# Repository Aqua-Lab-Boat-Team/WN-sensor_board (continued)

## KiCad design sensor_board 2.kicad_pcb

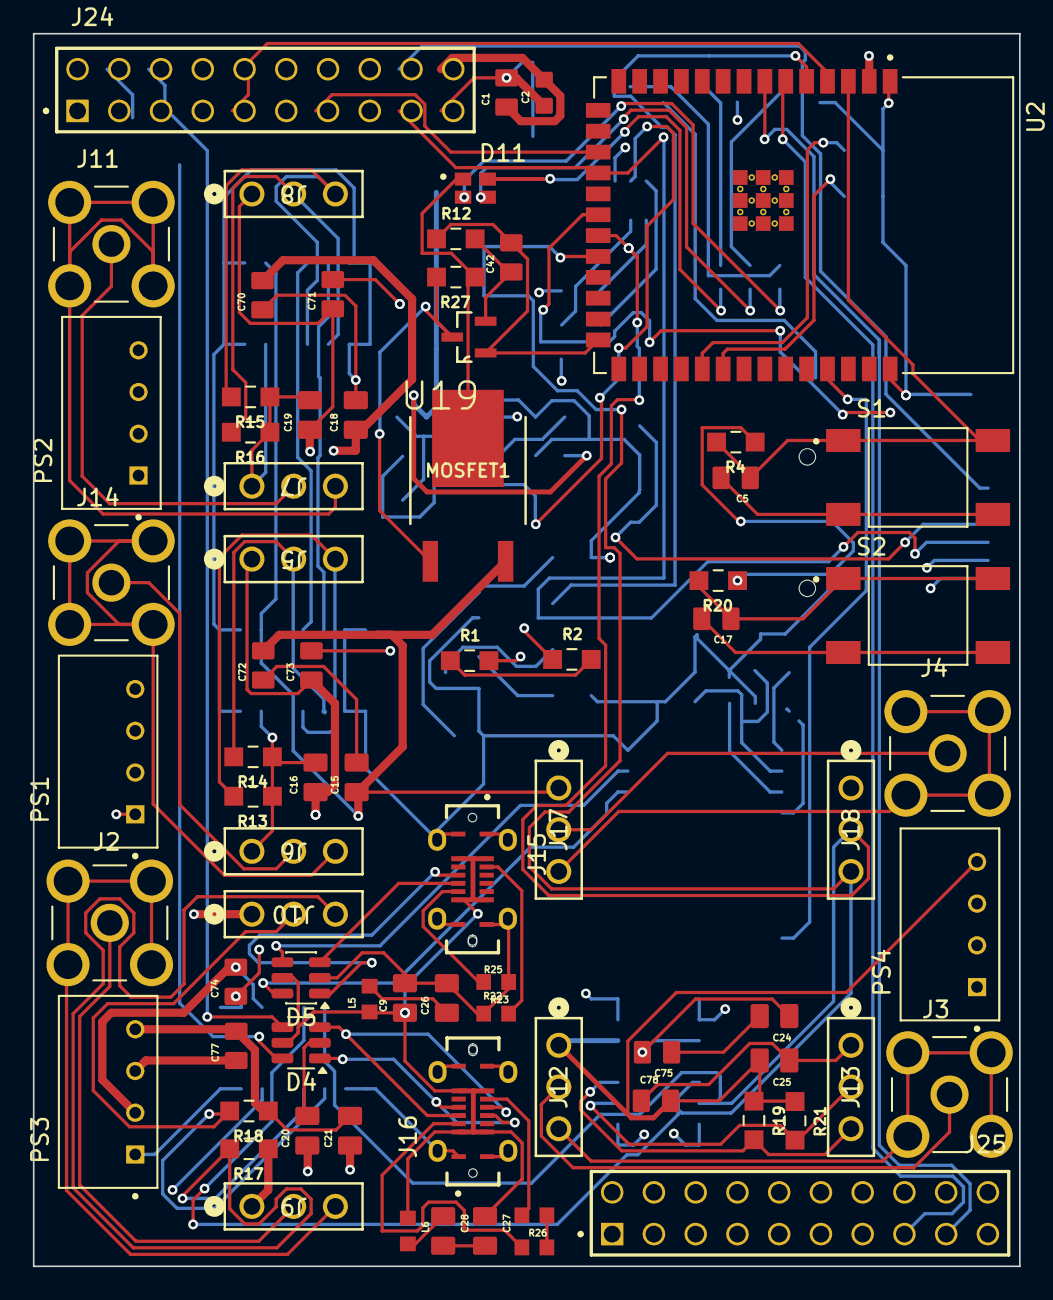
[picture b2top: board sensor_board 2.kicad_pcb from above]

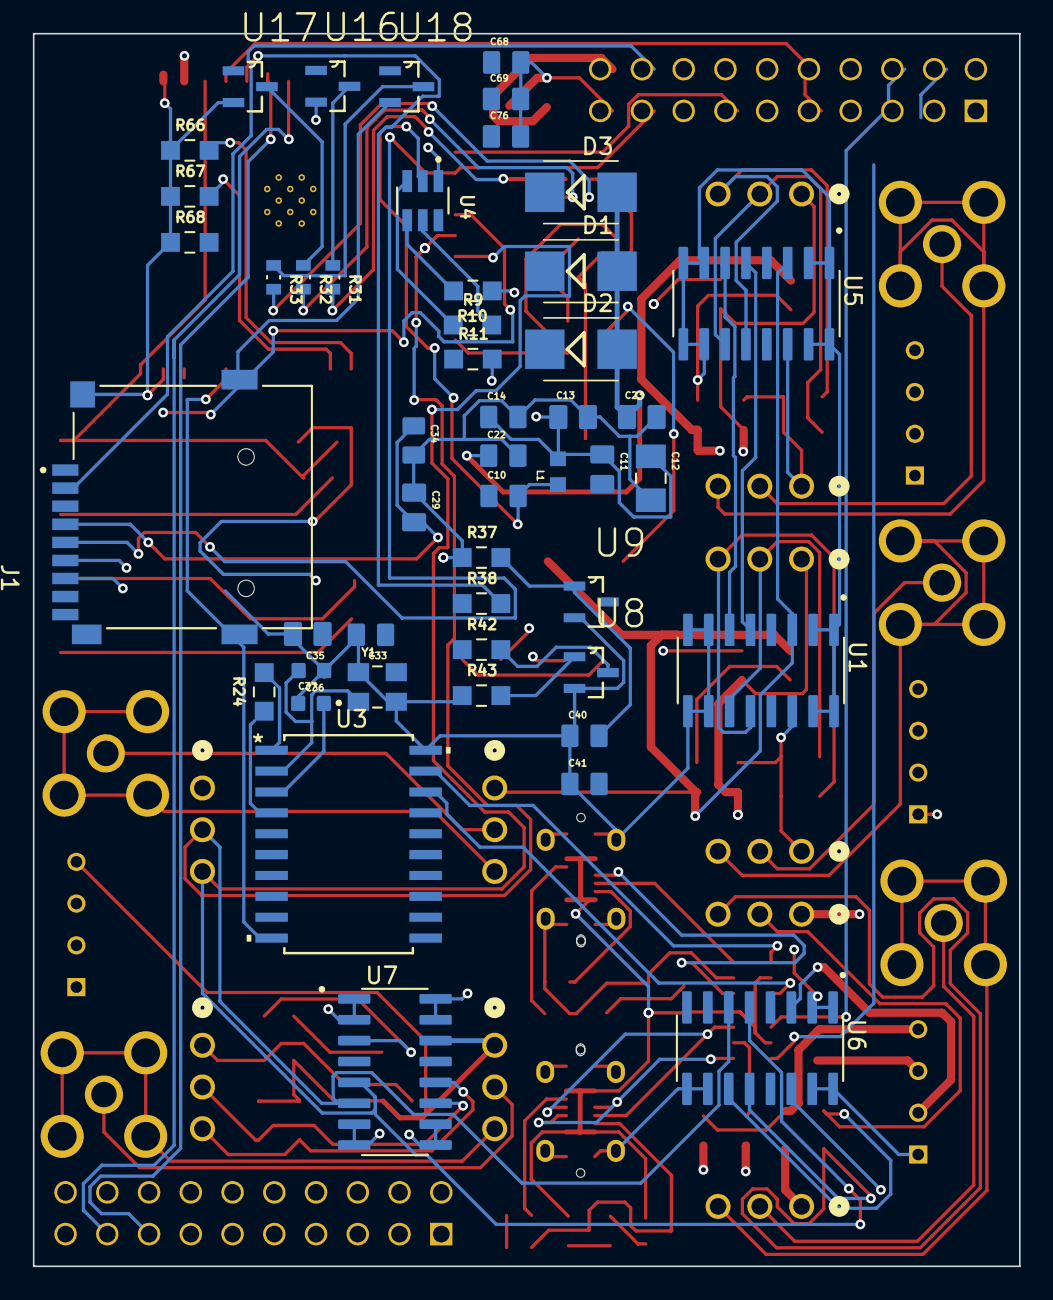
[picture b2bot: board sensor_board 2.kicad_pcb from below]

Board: 4 copper layers, 60.0 x 75.0 mm, 125 parts (49 on the bottom side), 95 nets.

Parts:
C1, C5, C10, C14, C17, C22: 0.1µ, 25V; CAPC2012X95N
C2: 22µ; CAPC1608X105N
C9, C26, C27, C28: 1µ, 25V; CAPC2012X145N
C11, C13, C15, C16, C18, C19, C20, C21, C23, C24, C25, C29: 10µ, 25V; CAPC2012X145N
C12: 47µ, 25V; CAPC3216X180N
C33, C34, C40, C41, C42, C68, C69, C70, C71, C72, C73, C74, C75, C76, C77, C78: 0.1uF 25V; CAPC2012X95N
C35: 10uF 25V; CAPC2012X145N
C36, C37: 18pF; CAPC1608X90N
D1, D2, D3: RB070MM-30TR; SMB
D4, D5: USBLC6-2SC6; SOT-23-6
D11: CLMVC-FKA-CL1D1L71BB7C3C3; LED_CLMVC-FKA-CL1D1L71BB7C3C3
J1: MSD-4-A; CUI_MSD-4-A
J2, J3, J4, J11, J14: RFPC-SMA28-F; GRADCONN_RFPC-SMA28-F
J5, J6, J7, J8, J9, J10, J12, J13, J17, J18: PPTC031LFBN-RC; CONN_PPTC031_SUL
J15, J16: USB4120-03-C_REVA6; GCT_USB4120-03-C_REVA6
J24, J25: TSW-110-07-F-D-LL; SAMTEC_TSW-110-07-F-D-LL
L1, L5, L6: 3.3µ; INDC1608X95N
MOSFET1: IRFR5505TRPBF; PG-TO252AA_INF
PS1, PS2, PS3, PS4: TBA_1-0310; CONV_TBA_1-0310
R1, R2: ERA6AEB104V; RES_ERA6AEB104V
R4, R9, R20: 100k; RES_ERA6AEB104V
R10: 31.6k; RES_ERA6AEB3162V
R11, R12, R13, R14, R15, R16, R17, R18, R19, R21, R27: 10k; RES_ERA6AEB103V
R22, R23, R25, R26: 5.1K; RESC1508X55N
R24, R38, R42, R66, R67, R68: 10K; RES_ERA6AEB103V
R31, R32, R33: 100 Ohm; RES_ERJ3EKF1000V
R37, R43: ERA6AEB304V; RES_ERA6AEB304V
S1, S2: TS04-66-50-BK-160-SMT-TR; SW_TS04-66-50-BK-160-SMT-TR
U1, U5, U6, U7: MAX14933ASE_T; SOIC127P600X175-16N
U2: ESP32-S3-WROOM-1-N8; XCVR_ESP32-S3-WROOM-1-N8
U3: MCP2200-I_SO; SOIC20
U4: AP62301WU-7; SOT95P280X100-6N
U8, U9, U16, U17, U18, U19: BSS123-7-F; SOT95P240X110-3N
Y1: ECS-120-12-33-AGN-TR; XTAL_ECS-120-12-33-AGN-TR

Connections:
+3V3: C1.1, C2.2, C11.1, C12.1, C13.1, C14.1, C33.1, C35.1, D11.1, J24.20, J25.18, J25.20, L1.2, MOSFET1.2, R4.1, R10.1, R20.1, R24.2, R27.1, R38.1, R42.1, U2.2 (3V3), U3.1 (VDD)
+3V3_S: C15.1, C18.1, C20.1, C24.1, C70.2, C72.2, C74.2, C75.2, J17.1, MOSFET1.3, PS1.2 (+VIN(VCC)), PS2.2 (+VIN(VCC)), PS3.2 (+VIN(VCC)), PS4.2 (+VIN(VCC)), U1.3 (VDDA), U5.3 (VDDA), U6.3 (VDDA), U7.3 (VDDA)
+ISO_3V3_1: C16.2, C73.2, J6.1, PS1.4 (+VOUT), R13.1, R14.1, U1.14 (VDDB)
+ISO_3V3_2: C19.2, C71.2, J7.1, PS2.4 (+VOUT), R15.1, R16.1, U5.14 (VDDB), U6.14 (VDDB)
+ISO_3V3_3: C21.2, C77.2, J9.1, PS3.4 (+VOUT), R17.1, R18.1
+ISO_3V3_4: C25.2, C78.2, J12.1, PS4.4 (+VOUT), R19.1, R21.1, U7.14 (VDDB)
+VBUSF_1: C28.1, D2.1, L6.2
+VBUSF_2: C26.1, D3.1, L5.2, U3.17 (VUSB)
/CS: J1.2 (CD/DAT3), J24.18, U2.19 (IO11)
/EXT_SIG: J25.16, R1.2
/IO1: J25.09, U2.39 (IO1)
/IO2: J25.11, U2.38 (IO2)
/IO3: J25.13, U2.15 (IO3)
/IO6: J25.15, U2.6 (IO6)
/IO7: J25.17, U2.7 (IO7)
/IO17: J25.02, U2.10 (IO17)
/IO18: J25.04, U2.11 (IO18)
/IO40: J25.06, U2.33 (IO40)
/IO41: J25.08, U2.34 (IO41)
/IO42: J25.10, U2.35 (IO42)
/IO47: J25.12, U2.24 (IO47)
/IO48: J25.14, U2.25 (IO48)
/ISO_SCL_1: J5.3, R13.2, U1.12 (I/OB1)
/ISO_SCL_2: J8.3, R15.2, U5.12 (I/OB1)
/ISO_SCL_3: J10.3, R17.2, U6.12 (I/OB1)
/ISO_SCL_4: J13.3, R19.2, U7.12 (I/OB1)
/ISO_SDA_1: J5.2, R14.2, U1.11 (I/OB2)
/ISO_SDA_2: J8.2, R16.2, U5.11 (I/OB2)
/ISO_SDA_3: J10.2, R18.2, U6.11 (I/OB2)
/ISO_SDA_4: J13.2, R21.2, U7.11 (I/OB2)
/LEAK_DET: C41.2, R43.2, U8.1 (G)
/LEAK_DET_OFFBD: C40.2, R37.2, U9.1 (G)
/LEAK_DET_OFFBD_S: J24.11, R38.2, U2.5 (IO5), U9.3 (D)
/LEAK_DET_S: J24.09, R42.2, U2.4 (IO4), U8.3 (D)
/MISO: J1.7 (DAT0), J24.13, U2.17 (IO9)
/MODE: C17.1, J24.03, R20.2, S2.1, S2.3, U2.27 (IO0)
/MOSI: J1.3 (CMD), J24.15, U2.12 (IO8)
/OFFBOARD_DET: J24.16, R1.1, R2.2, U2.23 (IO21)
/PGND1: J6.3, J14.G1, J14.G2, J14.G3, J14.G4
/PGND2: J7.3, J11.G1, J11.G2, J11.G3, J11.G4
/PGND3: J2.G1, J2.G2, J2.G3, J2.G4, J9.3
/PGND4: J3.G1, J3.G2, J3.G3, J3.G4, J12.3
/PRB1: J6.2, J14.1
/PRB2: J7.2, J11.1
/PRB3: J2.1, J9.2
/PRB4: J3.1, J12.2
/RGB_B: C68.1, J25.03, R67.2, U2.32 (IO39), U16.1 (G)
/RGB_G: C69.1, J25.01, R66.2, U2.31 (IO38), U17.1 (G)
/RGB_R: C76.1, J25.05, R68.2, U2.16 (IO46), U18.1 (G)
/SCK: J1.5 (CLK), J24.17, U2.18 (IO10)
/SCL: J18.3, J24.10, U1.5 (I/OA1), U2.22 (IO14), U5.5 (I/OA1), U6.5 (I/OA1), U7.5 (I/OA1)
/SDA: J18.2, J24.12, U1.6 (I/OA2), U2.21 (IO13), U5.6 (I/OA2), U6.6 (I/OA2), U7.6 (I/OA2)
/SD_DET: J1.CD, J24.14, U2.20 (IO12)
/SEN_POW: C42.2, J25.07, R12.1, U2.26 (IO45), U19.1 (G)
/SYS_RST: C5.1, J24.01, R4.2, S1.1, S1.3, U2.3 (EN)
/TEMP_PRB: J4.1, J17.2
/TEMP_PRB_GND: J4.G1, J4.G2, J4.G3, J4.G4, J17.3
/USB_CTS: J24.02, U2.8 (IO15), U3.13 (~CTS)
/USB_D2+: D5.4 (I/O2), U3.19 (D+)
/USB_D2-: D5.6 (I/O1), U3.18 (D-)
/USB_D+: D4.4 (I/O2), J24.06, U2.14 (IO20)
/USB_D-: D4.6 (I/O1), J24.04, U2.13 (IO19)
/USB_RTS: J24.08, U2.9 (IO16), U3.11 (~RTS)
/USB_RX: J24.05, U2.36 (RXD0), U3.12 (RX)
/USB_TX: J24.07, U2.37 (TXD0), U3.10 (TX)
GND: C1.2, C2.1, C5.2, C9.2, C12.2, C13.2, C14.2, C15.2, C17.2, C18.2, C20.2, C22.2, C23.2, C24.2, C26.2, C27.2, C28.2, C29.1, C33.2, C34.2, C35.2, C36.1, C37.1, C40.1, C41.1, C42.1, C68.2, C69.2, C70.1, C72.1, C74.1, C75.1, C76.2, D4.2 (GND), D5.2 (GND), J1.6 (VSS), J1.G1 (COVER_GND), J1.G2 (COVER_GND), J1.G3 (COVER_GND), J1.G4 (COVER_GND), J15.A1 (GND_A), J15.A12 (GND_A), J15.B1 (GND_B), J15.B12 (GND_B), J15.S1 (SHIELD), J15.S2 (SHIELD), J15.S3 (SHIELD), J15.S4 (SHIELD), J16.A1 (GND_A), J16.A12 (GND_A), J16.B1 (GND_B), J16.B12 (GND_B), J16.S1 (SHIELD), J16.S2 (SHIELD), J16.S3 (SHIELD), J16.S4 (SHIELD), J18.1, J24.19, J25.19, PS1.1 (-VIN(GND)), PS2.1 (-VIN(GND)), PS3.1 (-VIN(GND)), PS4.1 (-VIN(GND)), R2.1, R11.2, R12.2, R22.1, R23.1, R25.1, R26.1, R37.1, R43.1, R66.1, R67.1, R68.1, S1.2, S1.4, S2.2, S2.4, U1.1 (GNDA), U1.2 (I.C.), U1.7 (GNDA), U1.8 (I.C.), U1.9 (GNDB), U1.10 (I.C.), U1.15 (I.C.), U1.16 (GNDB), U2.1 (GND), U2.40 (GND), U3.20 (VSS), U4.1 (GND), U5.1 (GNDA), U5.2 (I.C.), U5.7 (GNDA), U5.8 (I.C.), U5.9 (GNDB), U5.10 (I.C.), U5.15 (I.C.), U5.16 (GNDB), U6.1 (GNDA), U6.2 (I.C.), U6.7 (GNDA), U6.8 (I.C.), U6.9 (GNDB), U6.10 (I.C.), U6.15 (I.C.), U6.16 (GNDB), U7.1 (GNDA), U7.2 (I.C.), U7.7 (GNDA), U7.8 (I.C.), U7.9 (GNDB), U7.10 (I.C.), U7.15 (I.C.), U7.16 (GNDB), U8.2 (S), U9.2 (S), U16.2 (S), U17.2 (S), U18.2 (S), U19.2 (S), Y1.2 (GND), Y1.4 (GND)
ISO_GND_1: C16.1, C73.1, J5.1, PS1.3 (-VOUT)
ISO_GND_2: C19.1, C71.1, J8.1, PS2.3 (-VOUT)
ISO_GND_3: C21.1, C77.1, J10.1, PS3.3 (-VOUT)
ISO_GND_4: C25.1, C78.1, J13.1, PS4.3 (-VOUT)
unnamed: D11.2, R31.2
unnamed: D11.3, R32.2
unnamed: D11.4, R33.2
unnamed: C29.2, C34.1, J1.4 (VDD)
unnamed: J15.A5 (CC1), R22.2
unnamed: J15.B5 (CC2), R23.2
unnamed: D5.3 (I/O2), J15.A6 (D1+), J15.B6 (D2+)
unnamed: D5.1 (I/O1), J15.A7 (D1-), J15.B7 (D2-)
unnamed: J16.A5 (CC1), R25.2
unnamed: J16.B5 (CC2), R26.2
unnamed: D4.3 (I/O2), J16.A6 (D1+), J16.B6 (D2+)
unnamed: D4.1 (I/O1), J16.A7 (D1-), J16.B7 (D2-)
unnamed: C36.2, U3.2 (OSC1), Y1.1 (IN/OUT)
unnamed: C37.2, U3.3 (OSC2), Y1.3 (OUT/IN)
unnamed: R24.1, U3.4 (RST)
unnamed: C10.1, U4.6 (BST)
unnamed: R9.2, U4.5 (EN)
unnamed: C11.2, R10.2, R11.1, U4.4 (FB)
unnamed: C10.2, L1.1, U4.2 (SW)
unnamed: R31.1, U16.3 (D)
unnamed: R32.1, U17.3 (D)
unnamed: R33.1, U18.3 (D)
unnamed: MOSFET1.1, R27.2, U19.3 (D)
VBUS_A: C9.1, C27.1, D4.5 (VBUS), D5.5 (VBUS), J15.A4 (VBUS_A), J15.A9 (VBUS_A), J15.B4 (VBUS_B), J15.B9 (VBUS_B), J16.A4 (VBUS_A), J16.A9 (VBUS_A), J16.B4 (VBUS_B), J16.B9 (VBUS_B), L5.1, L6.1
VSEL: C22.1, C23.1, D1.2, D2.2, D3.2, R9.1, U4.3 (VIN)
